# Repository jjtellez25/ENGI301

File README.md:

<h1>ENGI 301</h1>
Repository for ENGI301 course work

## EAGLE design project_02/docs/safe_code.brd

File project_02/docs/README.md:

<h1>README</h1>
Documents used to create PCB are found here

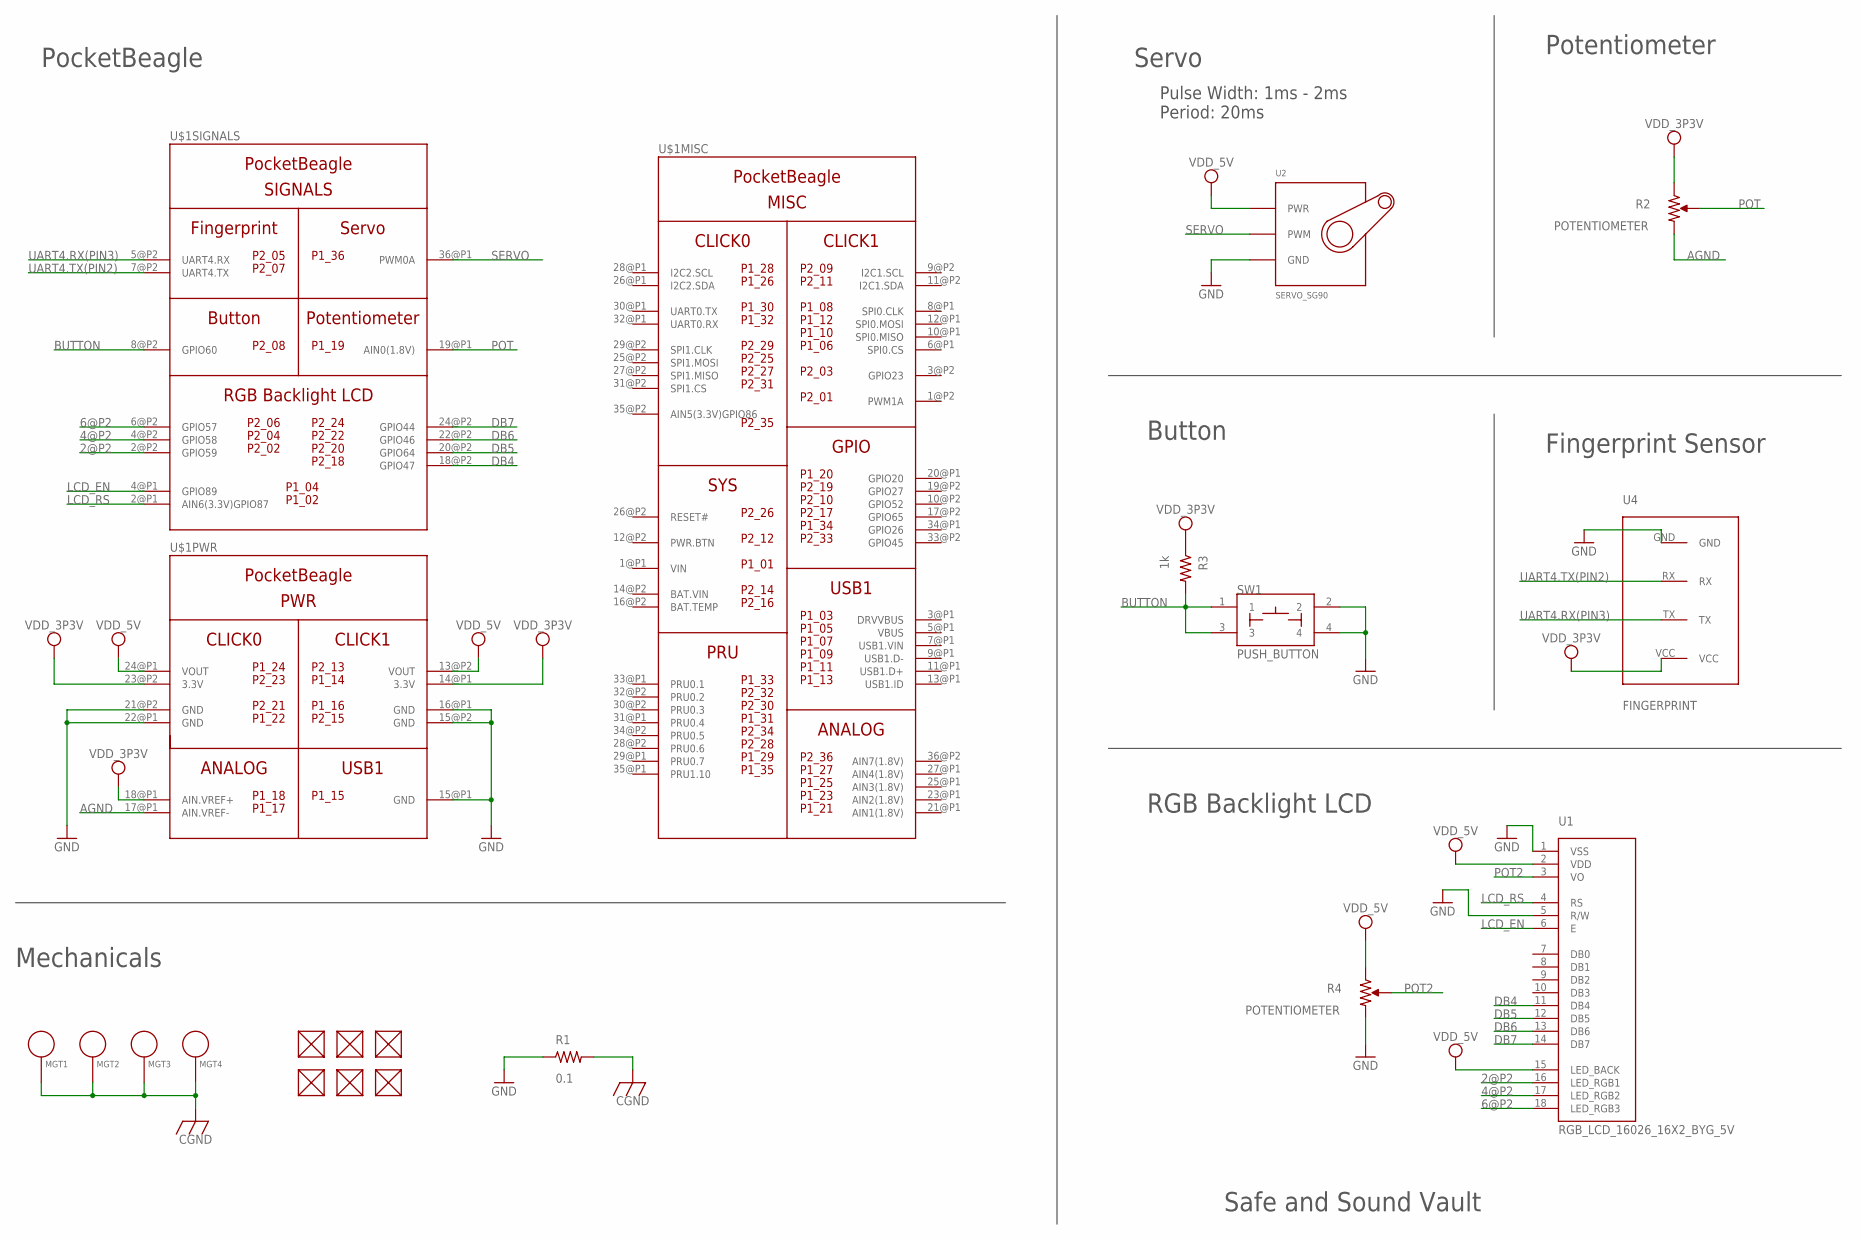
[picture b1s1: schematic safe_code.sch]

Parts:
FUD1, FUD2, FUD3, FUD4, FUD5, FUD6: FIDUCIAL; FIDUCIAL_40MIL
MGT1, MGT2, MGT3, MGT4: MOUNTING_HOLE
R1: 0.1; R0603
R2, R4: POTENTIOMETER; POT-PO90S
R3: 1k; R0603
SW1: PUSH_BUTTON; BUTTON_12.5MM
U1: RGB_LCD_16026_16X2_BYG_5V; RGB_LCD
U2: SERVO_SG90; SERVO-X1
U4: FINGERPRINT
U$1: POCKETBEAGLE_2

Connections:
2@P2: U1.16 (LED_RGB1), U$1.2@P2 (GPIO59)
4@P2: U1.17 (LED_RGB2), U$1.4@P2 (GPIO58)
6@P2: U1.18 (LED_RGB3), U$1.6@P2 (GPIO57)
AGND: R2.CW, U$1.17@P1 (AIN.VREF-)
BAT.VIN: U$1.14@P2 (BAT.VIN)
BUTTON: R3.2, SW1.1, SW1.3, U$1.8@P2 (GPIO60)
CGND: MGT1.P$1, MGT2.P$1, MGT3.P$1, MGT4.P$1, R1.2
DB4: U1.11 (DB4), U$1.18@P2 (GPIO47)
DB5: U1.12 (DB5), U$1.20@P2 (GPIO64)
DB6: U1.13 (DB6), U$1.22@P2 (GPIO46)
DB7: U1.14 (DB7), U$1.24@P2 (GPIO44)
GND: R1.1, R4.CW, SW1.2, SW1.4, U1.1 (VSS), U1.5 (R/W), U2.GND, U4.GND, U$1.15@P1 (GND), U$1.15@P2 (GND), U$1.16@P1 (GND), U$1.21@P2 (GND), U$1.22@P1 (GND)
LCD_EN: U1.6 (E), U$1.4@P1 (GPIO89)
LCD_RS: U1.4 (RS), U$1.2@P1 (AIN6(3.3V)GPIO87)
POT: R2.S, U$1.19@P1 (AIN0(1.8V))
POT2: R4.S, U1.3 (VO)
SERVO: U2.SIG (PWM), U$1.36@P1 (PWM0A)
UART4.RX(PIN3): U4.TX, U$1.5@P2 (UART4.RX)
UART4.TX(PIN2): U4.RX, U$1.7@P2 (UART4.TX)
VDD_3P3V: R2.CCW, R3.1, U4.VCC, U$1.14@P1 (3.3V), U$1.18@P1 (AIN.VREF+), U$1.23@P2 (3.3V)
VDD_5V: R4.CCW, U1.2 (VDD), U1.15 (LED_BACK), U2.PWR, U$1.24@P1 (VOUT)
VIN: U$1.1@P1 (VIN)

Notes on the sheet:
PocketBeagle
Pulse Width: 1ms - 2ms Period: 20ms
Potentiometer
Button
Fingerprint Sensor
RGB Backlight LCD
Servo
Mechanicals
Safe and Sound Vault

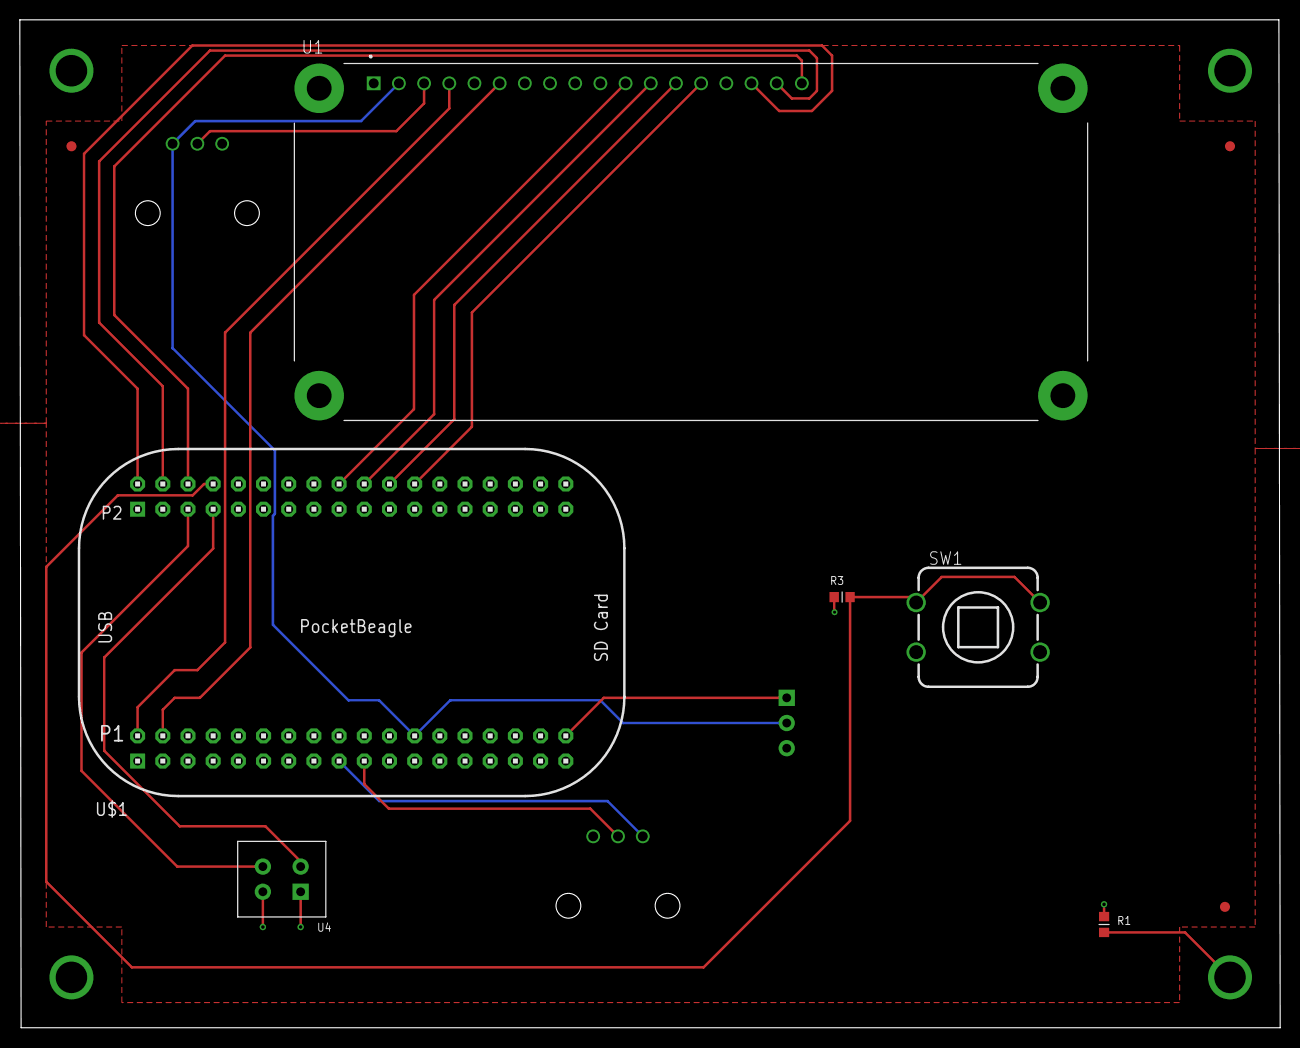
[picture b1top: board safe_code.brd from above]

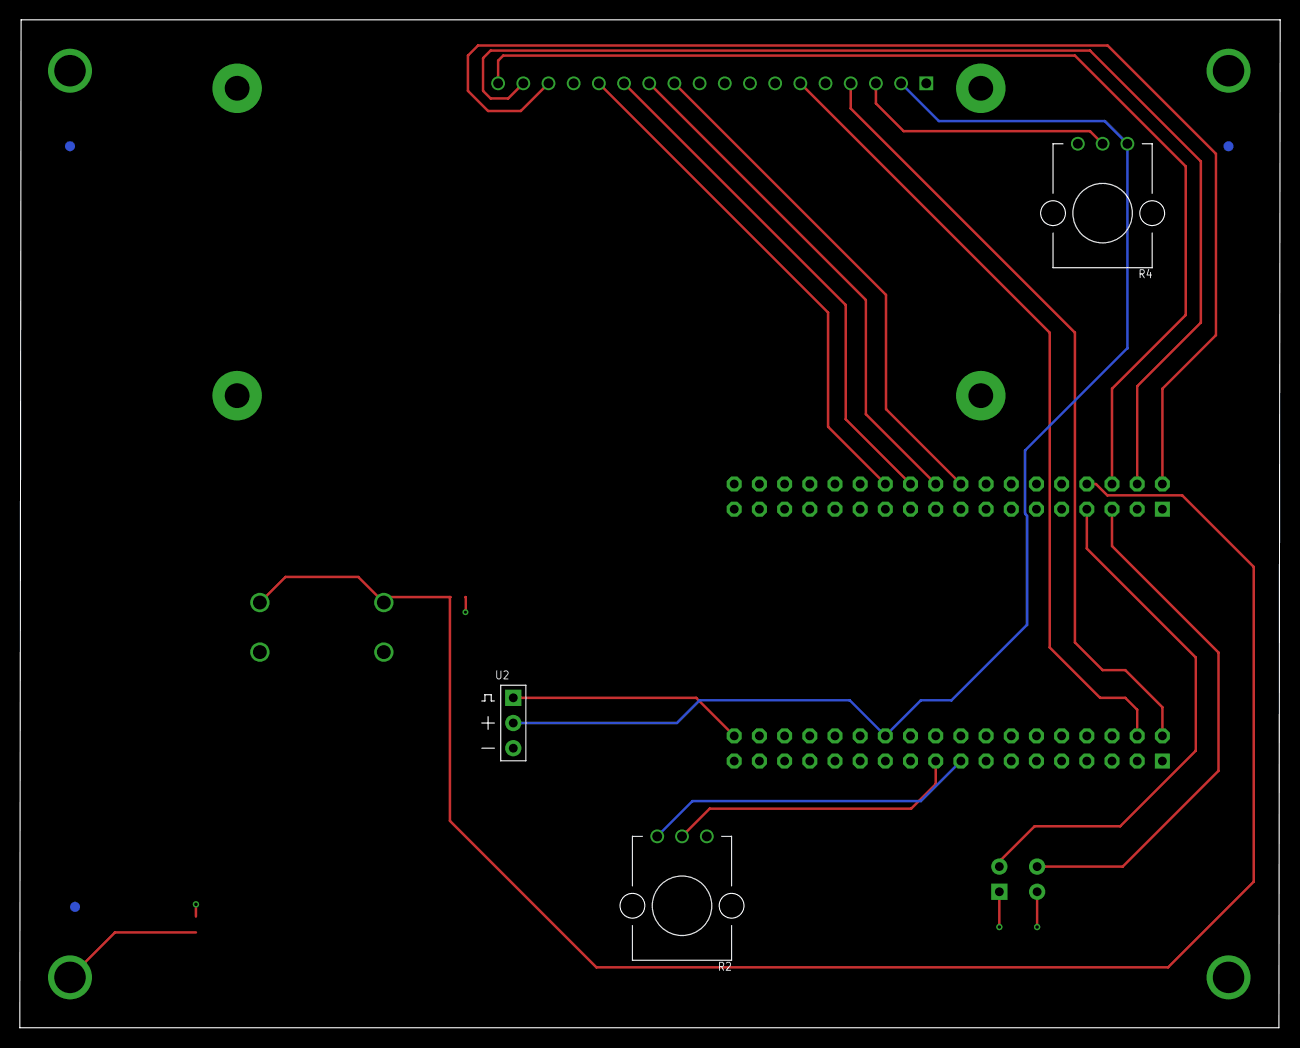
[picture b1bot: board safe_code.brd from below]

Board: 4 copper layers, 127.1 x 101.7 mm, 19 parts (6 on the bottom side), 20 nets.

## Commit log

2023-09-26 Create simple_calc
2023-09-26 Create calc
2023-09-26 simple_calc.py
2023-09-26 blink_USR3.py
2023-10-02 Updated presentation
2023-10-12 Software Diagram
2023-11-20 adding files for project 1
2023-12-04 Create project_02
2023-12-14 Create Price Quotes
2023-12-14 Create mfg folder
2023-12-14 Upload library, schematic and board
2023-12-14 Upload assembly and BOM
2023-12-14 Create dcs
2023-12-14 Create safe_code
2023-12-14 Added files via upload
2023-12-14 Create cdcs
2023-12-14 Create xsa
2023-12-14 Create cbsj
2023-12-14 Update Price Quotes
2023-12-14 Rename Price Quotes to Price Quotes.md
